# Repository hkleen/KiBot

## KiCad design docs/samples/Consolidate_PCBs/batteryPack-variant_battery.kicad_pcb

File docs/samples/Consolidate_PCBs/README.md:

# Consolidate PCB example

Here we have 3 PCBs:

- *batteryPack-variant_battery.kicad_pcb*
- *batteryPack-variant_charger.kicad_pcb*
- *batteryPack-variant_connector.kicad_pcb*

And we want to create a new PCB containing them using the layout found in
*batteryPack_new_layout.kicad_pcb*

So we use the following *consolidate_pcb.kibot.yaml*:

```yaml
kibot:
  version: 1

preflight:
  consolidate_pcbs:
    - name: Battery
      file: batteryPack-variant_battery.kicad_pcb
    - name: Charger
      file: batteryPack-variant_charger.kicad_pcb
    - name: Connector
      file: batteryPack-variant_connector.kicad_pcb
```

Note that the names (Battery, Charger and Connector) are the names used inside
the text boxes in *batteryPack_new_layout.kicad_pcb*

After running this script, i.e.:

```
kibot -b batteryPack_new_layout.kicad_pcb
```

The *batteryPack_new_layout.kicad_pcb* will be replaced by the desired PCB.
The old PCB is renamed to *batteryPack_new_layout.kicad_pcb-bak*.

This new PCB can be used to create a 3D render containing the 3 PCBs.

# Note about the 3 PCBs

These PCBs were generated using the *batteryPack.kicad_pcb* example and the
following config:

```yaml
kibot:
  version: 1

variants:
  - name: 'default'
    comment: 'Default variant'
    type: ibom
    sub_pcbs:
      - name: charger
        tlx: 175
        tly: 30
        brx: 258
        bry: 92
      - name: battery
        tlx: 10
        tly: 20
        brx: 110
        bry: 121
      - name: connector
        tlx: 100
        tly: 28
        brx: 160
        bry: 113

outputs:
  - name: 'pcb_charger'
    comment: "PCB for the charger"
    type: pcb_variant
    options:
      variant: default[charger]
      title: 'Charger'

  - name: 'pcb_battery'
    comment: "PCB for the battery"
    type: pcb_variant
    options:
      variant: default[battery]
      title: 'Battery'

  - name: 'pcb_connector'
    comment: "PCB for the connector"
    type: pcb_variant
    options:
      variant: default[connector]
      title: 'Connector'
```

So KiBot can do both things:

- Split a PCB
- Merge PCBs

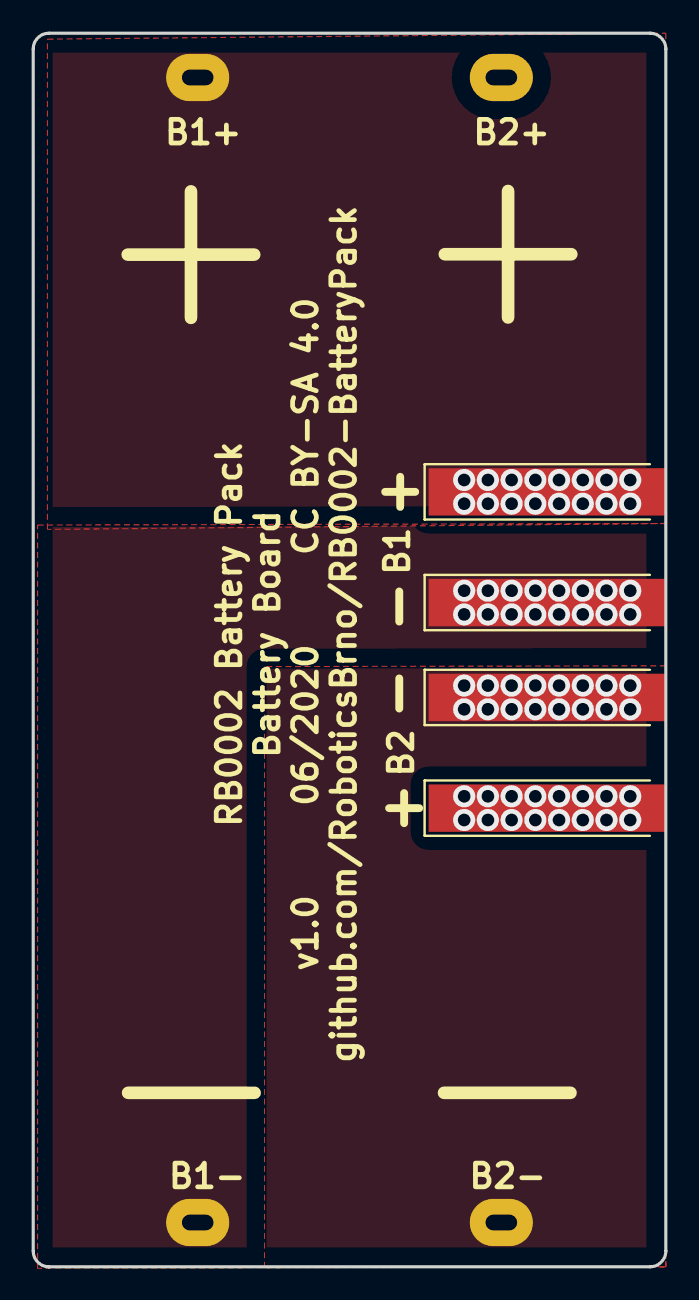
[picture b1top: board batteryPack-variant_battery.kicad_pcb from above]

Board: 2 copper layers, 40.0 x 78.0 mm, 5 parts (1 on the bottom side), 4 nets, no tracks yet.

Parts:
BT1: BK-18650-PC4; BAT_BK-18650-PC4
J9: B2+; 2mm_Banana-Socket
J10: B1+; 2mm_Banana-Socket
J11: B1-; 2mm_Banana-Socket
J12: B2-; 2mm_Banana-Socket

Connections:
/BP_B1+: BT1.1+, J10.1
/BP_B1-: BT1.1, J11.1
/BP_B2+: BT1.2+, J9.1
/BP_B2-: BT1.2, J12.1

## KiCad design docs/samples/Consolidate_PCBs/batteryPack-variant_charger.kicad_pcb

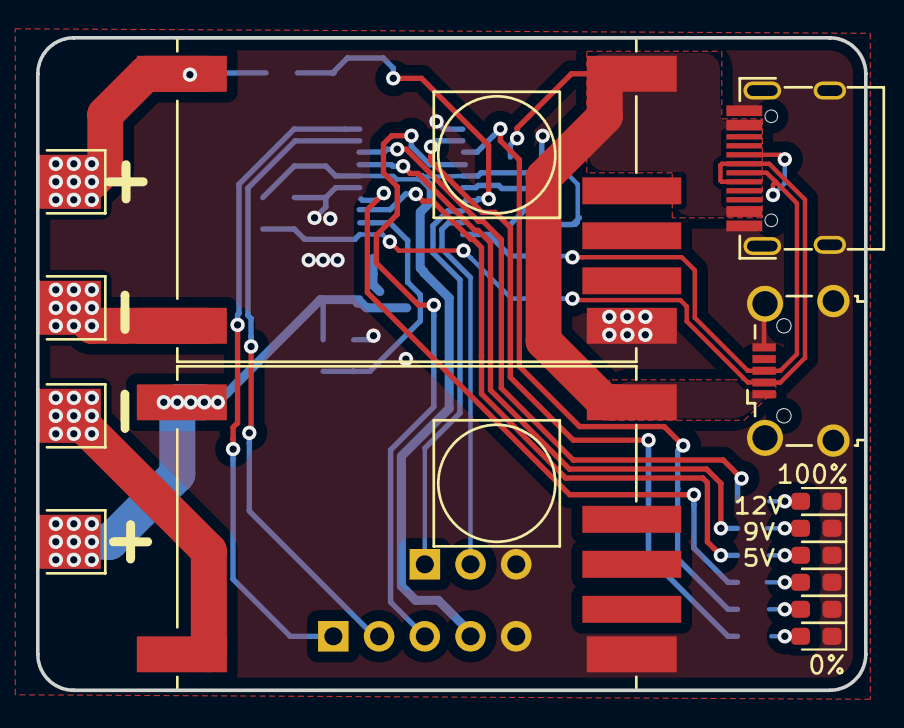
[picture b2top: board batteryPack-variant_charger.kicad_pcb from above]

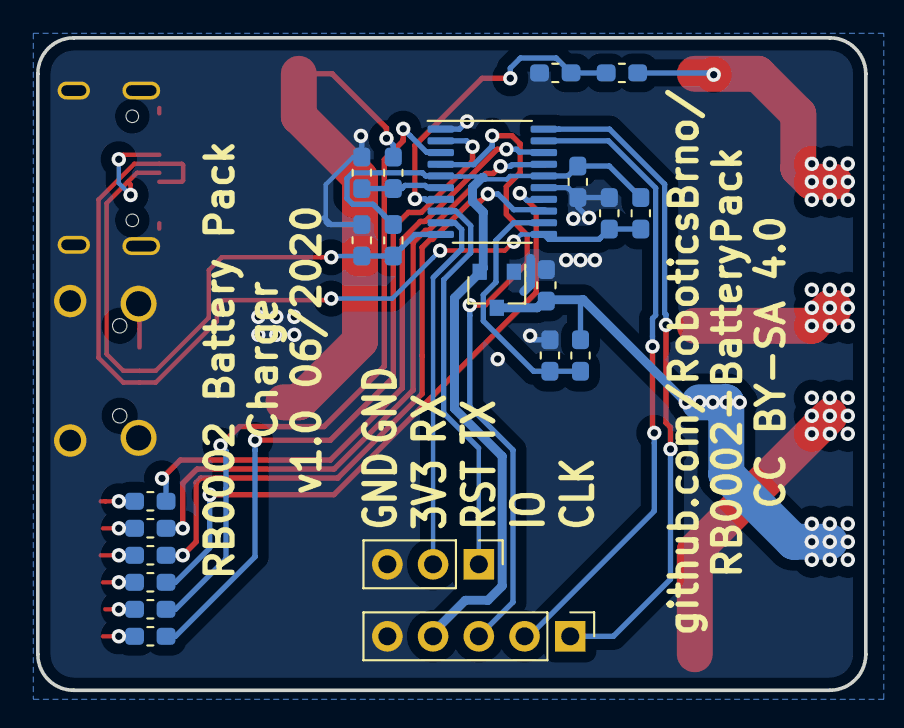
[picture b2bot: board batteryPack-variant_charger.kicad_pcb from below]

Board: 2 copper layers, 46.0 x 36.2 mm, 36 parts (22 on the bottom side), 29 nets.

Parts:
C1, C2: 470n; C_0603_1608Metric_Pad1.05x0.95mm_HandSolder
D1: LED_5V; LED_0603_1608Metric_Pad1.05x0.95mm_HandSolder
D2: LED_9V; LED_0603_1608Metric_Pad1.05x0.95mm_HandSolder
D3: LED_12V; LED_0603_1608Metric_Pad1.05x0.95mm_HandSolder
D4: LED_40%; LED_0603_1608Metric_Pad1.05x0.95mm_HandSolder
D5: LED_20%; LED_0603_1608Metric_Pad1.05x0.95mm_HandSolder
D6: LED_0%; LED_0603_1608Metric_Pad1.05x0.95mm_HandSolder
J1: Mirco USB; USB_Micro-B_Wuerth_629105150521_CircularHoles
J7: SWD; PinHeader_1x05_P2.54mm_Vertical
J8: UART; PinHeader_1x03_P2.54mm_Vertical
J13: B1+; 2mm_Banana-Plug
J14: B1-; 2mm_Banana-Plug
J15: B2+; 2mm_Banana-Plug
J16: B2-; 2mm_Banana-Plug
P1: USB-C; USB_C_Female-16Pin-HPJF
R1, R3, R9, R10, R12: 10k; R_0603_1608Metric_Pad1.05x0.95mm_HandSolder
R2, R4: 2k4; R_0603_1608Metric_Pad1.05x0.95mm_HandSolder
R5, R6, R7, R14, R15, R16: 1k; R_0603_1608Metric_Pad1.05x0.95mm_HandSolder
R8: 62k; R_0603_1608Metric_Pad1.05x0.95mm_HandSolder
R11, R13: 20k; R_0603_1608Metric_Pad1.05x0.95mm_HandSolder
U1, U4: TP5100-Module
U2: STM32F030F4Px; TSSOP-20_4.4x6.5mm_P0.65mm
U3: XC6206P332MR; SOT-23

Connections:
+3V3: C1.2, J7.4, R1.1, R3.1, U2.5, U2.16, U3.2
/VBUS_SENSE: R8.2, R9.1, U2.6
BAT1+: J13.1, R12.1, U1.3
BAT1_V: R12.2, R13.1, U2.7
BAT2+: C2.2, J15.1, R10.1, U3.3, U4.3
BAT2_V: R10.2, R11.1, U2.12
D+: J1.3, P1.A6, P1.B6, R3.2, R4.1, U2.10
D-: J1.2, P1.A7, P1.B7, R1.2, R2.1, U2.11
GND: C1.1, C2.1, D1.1, D2.1, D3.1, D4.1, D5.1, D6.1, J1.5, J1.6, J7.5, J8.3, P1.A1, P1.A12, P1.B1, P1.B12, P1.S1, R2.2, R4.2, R9.2, R11.2, R13.2, U1.1, U2.1, U2.15, U3.1, U4.1
unnamed: D1.2, R5.2
unnamed: D2.2, R6.2
unnamed: D3.2, R7.2
unnamed: D4.2, R14.2
unnamed: D5.2, R15.2
unnamed: D6.2, R16.2
unnamed: J14.1, U1.4
unnamed: J16.1, U4.4
unnamed: R5.1, U2.13
unnamed: R6.1, U2.17
unnamed: R7.1, U2.18
unnamed: R14.1, U2.14
unnamed: R15.1, U2.3
unnamed: R16.1, U2.2
RST: J7.3, U2.4
RX: J8.2, U2.9
SWCLK: J7.1, U2.20
SWDIO: J7.2, U2.19
TX: J8.1, U2.8
VBUS: J1.1, P1.A4, P1.A9, P1.B4, P1.B9, R8.1, U1.2, U4.2

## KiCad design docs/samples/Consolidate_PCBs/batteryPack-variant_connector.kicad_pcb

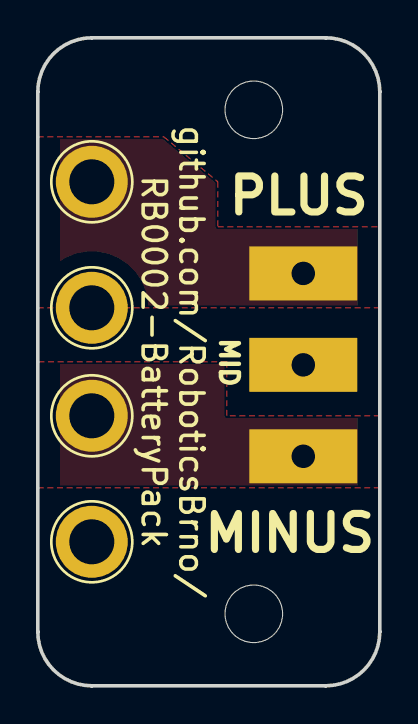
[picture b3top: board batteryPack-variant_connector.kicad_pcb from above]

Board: 2 copper layers, 19.0 x 36.0 mm, 7 parts (0 on the bottom side), 3 nets, no tracks yet.

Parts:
H1, H2: MountingHole; MountingHole_3.2mm_M3
J2: B1+; 2mm_Banana-Vertical
J3: B1-; 2mm_Banana-Vertical
J4: B2-; 2mm_Banana-Vertical
J5: B2+; 2mm_Banana-Vertical
J6: CableConnector; Terminal_1x03_P5.08mm_Horizontal

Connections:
/MID: J3.1, J5.1, J6.2
/OUT+: J2.1, J6.3
/OUT-: J4.1, J6.1

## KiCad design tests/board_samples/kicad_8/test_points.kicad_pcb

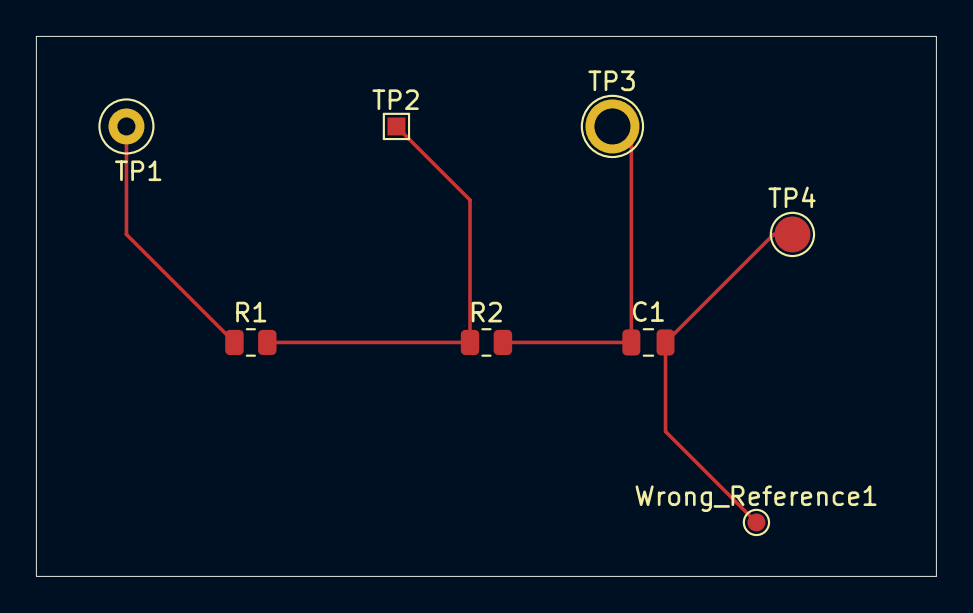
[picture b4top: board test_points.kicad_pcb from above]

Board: 2 copper layers, 50.0 x 30.0 mm, 8 parts (0 on the bottom side), 4 nets.

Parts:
C1: 1uF; C_0805_2012Metric
R1: 10; R_0805_2012Metric
R2: 20; R_0805_2012Metric
TP1: TestPoint; TestPoint_Loop_D1.80mm_Drill1.0mm_Beaded
TP2: TestPoint_Alt; TestPoint_Pad_1.0x1.0mm
TP3: TestPoint_Flag; TestPoint_Plated_Hole_D2.0mm
TP4: TestPoint_Probe; TestPoint_Pad_D2.0mm
Wrong_Reference1: TestPoint_Small; TestPoint_Pad_D1.0mm

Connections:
unnamed: C1.1, R2.2, TP3.1
unnamed: C1.2, TP4.1, Wrong_Reference1.1
unnamed: R1.1, TP1.1
unnamed: R1.2, R2.1, TP2.1

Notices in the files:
docs/samples/Consolidate_PCBs/batteryPack-variant_battery.kicad_pcb:
v1.0 06/2020 CC BY-SA 4.0
docs/samples/Consolidate_PCBs/batteryPack-variant_charger.kicad_pcb:
CC BY-SA 4.0
